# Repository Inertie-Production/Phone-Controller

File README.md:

# Phone Controller

This is a phone controller design inspired by the Nintendo 3DS. We created this controller because we wanted to make a cheap and pocketable phone controller while learning a lot of new stuff in the process! 
You can view and download the 3D model [on our Onshape][onshape].

On this github, you will find the pcb source files & gerbers, the code that
needs to be loaded on the controller and a BOM.

Once built, to use this controller, you can just clamp your phone on it, turn the power on with the switch and connect to it via bluetooth. 
Despite being very thin, this controller includes all the features of a full-size controller :
- 11 buttons with silent mechanical switches
- A D-pad
- 2 dual-axis joysticks
- 2 analog Hall effect triggers or 2 mechanical switches triggers
The 4 buttons on the back of the controller are the sticks buttons and the bumpers.

Every file of this repository and the Onshape project are licensied under the
GPL v3 license, see [`LICENSE`](./LICENSE) for details.

[onshape]: https://cad.onshape.com/documents/3e0c9ef397f91415fa372e0c/w/6f6e95703b5b2ee9676d2bfe/e/8a00a41f1ee7d469ca8e343f?renderMode=0&uiState=69529d2b1ac4d36407fdba0f

## Screenshots

## BOM

| Type | Name | Description | Qtt needed | Link |
|------|------|-------------|------------|------|
|Sticks|New 3DS XL Sticks|Nintendo new 3DS XL joysticks|2|2: https://www.alibaba.com/product-detail/Analog-Joystick-for-New-3DS-XL_1600274819879.html ; https://fr.aliexpress.com/item/1005006359586643.html + https://www.alibaba.com/product-detail/Thumb-Stick-for-3DS-3DS-XL_1601603454755.html?spm=a2700.prosearch.normal_offer.d_image.439067af8KJ20J&priceId=0518491792cb4dbdbbd4ce53df52cdd5 |
|Screws|M1.4|Nintendo 3DS joystick screws (8mm Long x 1.5mm x 2.5mm) | 4 | https://fr.aliexpress.com/item/1005002364189187.html |
| | M2|4mm countersunk screws (for closing the back panel)|9|https://fr.aliexpress.com/item/1005008709978631.html |
||M2.5|5mm round/dome screws (max head height: 1.8mm) to fix the PCB|5|https://fr.aliexpress.com/item/1005008709978631.html |
|Buttons|SS-12D00 |SS-12D00 2mm shaft slide switch (power)|1|https://fr.aliexpress.com/item/1005008489387043.html |
||Buttons|6x6x3.5mm 2 pins (silent) mouse switches (ex: HUANO Mute Button 6 × 6 × 3.5mm; Kailh Mini 6.2mm Silent Micro Switches)|11|https://fr.aliexpress.com/item/1005005681410178.html |
||SKRWADE030|SKRWADE030 tactile buttons|4|https://fr.aliexpress.com/item/4001125555481.html |
|Triggers|SS49E|SS49E Hall effect sensors|2|https://fr.aliexpress.com/item/1005006001710265.html |
||Magnets|round 5x2mm magnets|2|https://fr.aliexpress.com/item/1005010155029417.html |
||Springs|springs (15×4mm)|2|https://fr.aliexpress.com/item/1005005402501364.html |
|Electronic|603030|603030 LiPo battery (30 × 30 × 6mm)|1|https://www.alibaba.com/product-detail/Lipo-603030-3-7V-600mAh-Rechargeable_1601168807381.html ; https://fr.aliexpress.com/item/1005007958724149.html |
||Resistors|10kΩ resistor (0805)|4|https://fr.aliexpress.com/item/1005006144658512.html |
|||200 kΩ resistors (0805)|2|https://fr.aliexpress.com/item/1005008666573344.html |
||BAT54C|BAT54C diodes|8|https://fr.aliexpress.com/item/1005006228736157.html |
||Seeed studio|Seeed Studio XIAO ESP32-S3 Plus and an antenna|1|https://www.seeedstudio.com/Seeed-Studio-XIAO-ESP32S3-Plus-p-6361.html ; https://fr.aliexpress.com/item/1005008329745247.html |
||100 nF 0805|100 nF capacitor (0805)|1|https://fr.aliexpress.com/item/1005006142309480.html
||PCB|The PCB|1|https://cart.jlcpcb.com/fr/quote?stencilLayer=2&stencilWidth=100&stencilLength=100&stencilCounts=5&plateType=1&spm=Jlcpcb.Homepage.1010 |
|Plastic|3D printer filament|in grams, full estimation to check|300|

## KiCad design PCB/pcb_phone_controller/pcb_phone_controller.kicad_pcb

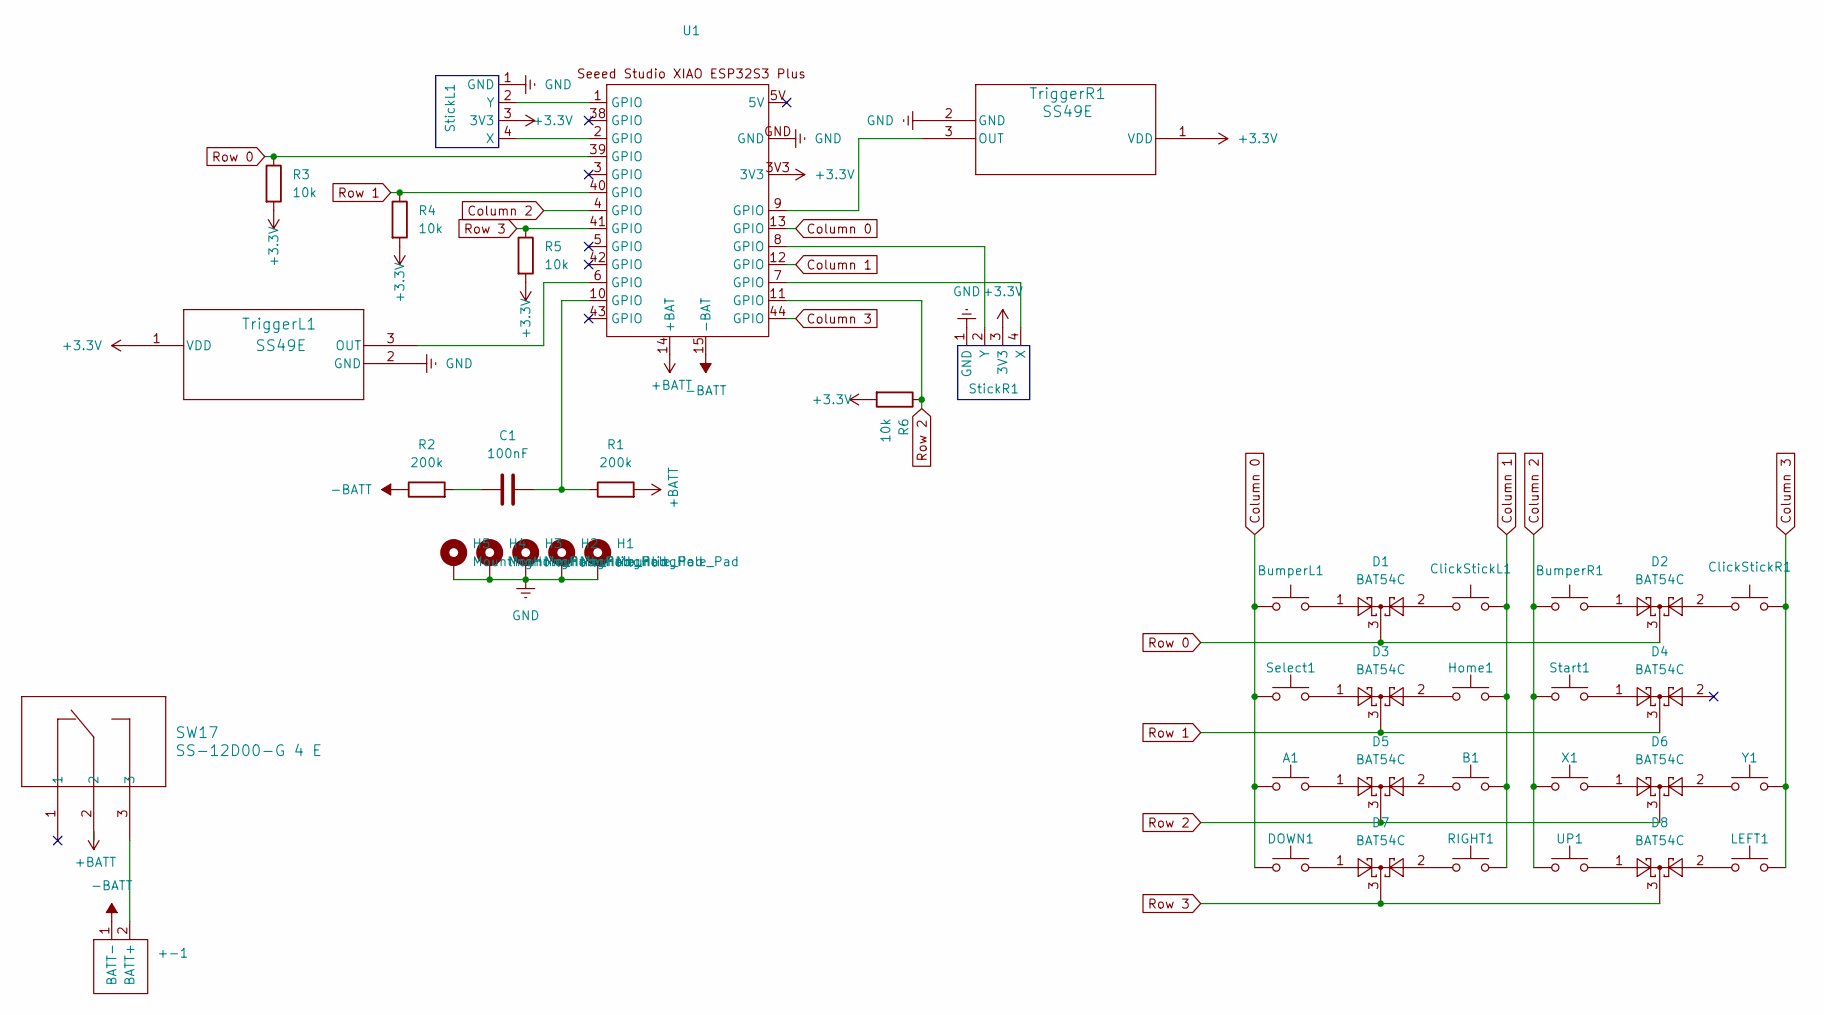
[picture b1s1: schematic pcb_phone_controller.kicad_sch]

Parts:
+-1: Battery_connection
A1: KAILH-MINI-SILENT-SWITCH
B1: KAILH-MINI-SILENT-SWITCH
BumperL1: Thin membrane button; SKRWADE030
BumperR1: Thin membrane button; SKRWADE030
C1: 100nF; C_0805_2012Metric_Pad1.18x1.45mm_HandSolder
ClickStickL1: Thin membrane button; SKRWADE030
ClickStickR1: Thin membrane button; SKRWADE030
D1, D2, D3, D4, D5, D6, D7, D8: BAT54C; SOT-23
DOWN1: KAILH-MINI-SILENT-SWITCH
H1, H2, H3, H4, H5: MountingHole_Pad; MountingHole_2.7mm_M2.5_ISO14580_Pad
Home1: KAILH-MINI-SILENT-SWITCH
LEFT1: KAILH-MINI-SILENT-SWITCH
R1, R2: 200k; R_0805_2012Metric_Pad1.20x1.40mm_HandSolder
R3, R4, R5, R6: 10k; R_0805_2012Metric_Pad1.20x1.40mm_HandSolder
RIGHT1: KAILH-MINI-SILENT-SWITCH
SW17: SS-12D00-G 4 E; 1P2T_SS-12D00_CNK
Select1: KAILH-MINI-SILENT-SWITCH
Start1: KAILH-MINI-SILENT-SWITCH
StickL1: PinHeader_1x04_P2.54mm_Vertical
StickR1: PinHeader_1x04_P2.54mm_Vertical
TriggerL1: SS49E; ss49e
TriggerR1: SS49E; ss49e
U1: Seeed Studio XIAO ESP32S3 Plus
UP1: KAILH-MINI-SILENT-SWITCH
X1: KAILH-MINI-SILENT-SWITCH
Y1: KAILH-MINI-SILENT-SWITCH

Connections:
+3.3V: R3.2, R4.2, R5.2, R6.2, StickL1.3 (3V3), StickR1.3 (3V3), TriggerL1.1 (VDD), TriggerR1.1 (VDD), U1.3V3
+BATT: R1.2, SW17.2, U1.14 (+BAT)
-BATT: +-1.1 (BATT-), R2.1, U1.15 (-BAT)
Column 0: A1.1, BumperL1.1, DOWN1.1, Select1.1, U1.13 (GPIO)
Column 1: B1.2, ClickStickL1.2, Home1.2, RIGHT1.2, U1.12 (GPIO)
Column 2: BumperR1.1, Start1.1, U1.4 (GPIO), UP1.1, X1.1
Column 3: ClickStickR1.2, LEFT1.2, U1.44 (GPIO), Y1.2
GND: H1.1, H2.1, H3.1, H4.1, H5.1, StickL1.1 (GND), StickR1.1 (GND), TriggerL1.2 (GND), TriggerR1.2 (GND), U1.GND
unnamed: +-1.2 (BATT+), SW17.3
unnamed: A1.2, D5.1
unnamed: B1.1, D5.2
unnamed: BumperL1.2, D1.1
unnamed: BumperR1.2, D2.1
unnamed: C1.1, R1.1, U1.10 (GPIO)
unnamed: C1.2, R2.2
unnamed: ClickStickL1.1, D1.2
unnamed: ClickStickR1.1, D2.2
unnamed: D3.1, Select1.2
unnamed: D3.2, Home1.1
unnamed: D4.1, Start1.2
unnamed: D6.1, X1.2
unnamed: D6.2, Y1.1
unnamed: D7.1, DOWN1.2
unnamed: D7.2, RIGHT1.1
unnamed: D8.1, UP1.2
unnamed: D8.2, LEFT1.1
unnamed: StickL1.4 (X), U1.2 (GPIO)
unnamed: StickL1.2 (Y), U1.1 (GPIO)
unnamed: StickR1.4 (X), U1.7 (GPIO)
unnamed: StickR1.2 (Y), U1.8 (GPIO)
unnamed: TriggerL1.3 (OUT), U1.6 (GPIO)
unnamed: TriggerR1.3 (OUT), U1.9 (GPIO)
Row 0: D1.3, D2.3, R3.1, U1.39 (GPIO)
Row 1: D3.3, D4.3, R4.1, U1.40 (GPIO)
Row 2: D5.3, D6.3, R6.1, U1.11 (GPIO)
Row 3: D7.3, D8.3, R5.1, U1.41 (GPIO)

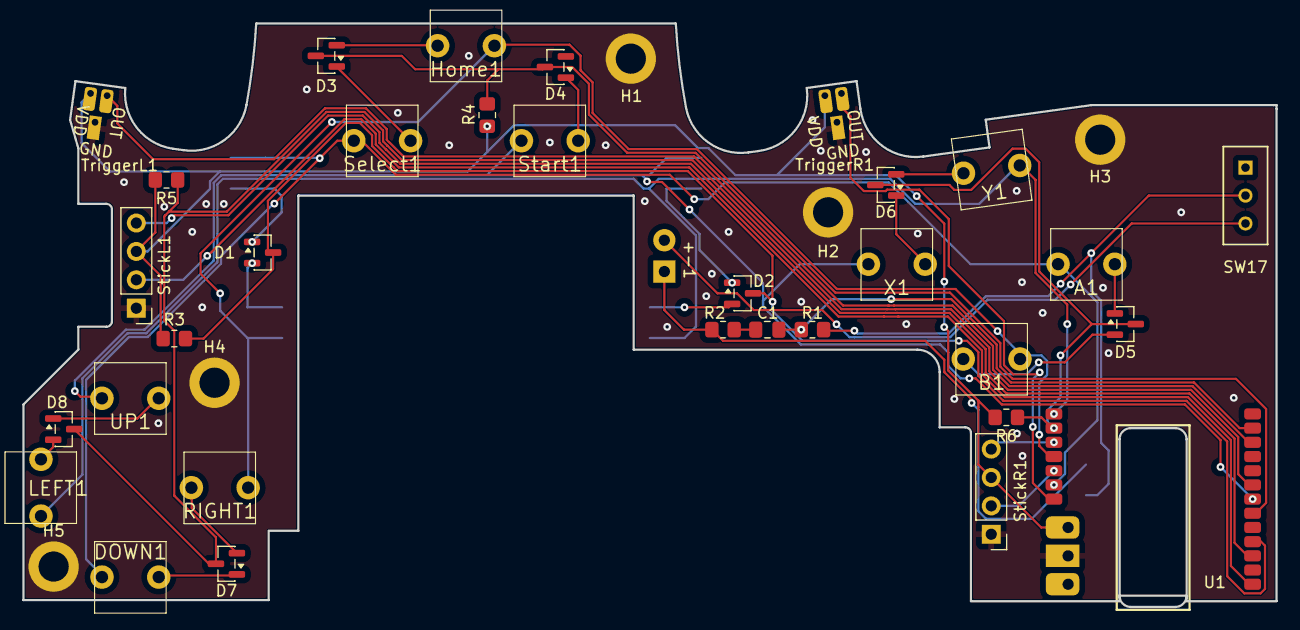
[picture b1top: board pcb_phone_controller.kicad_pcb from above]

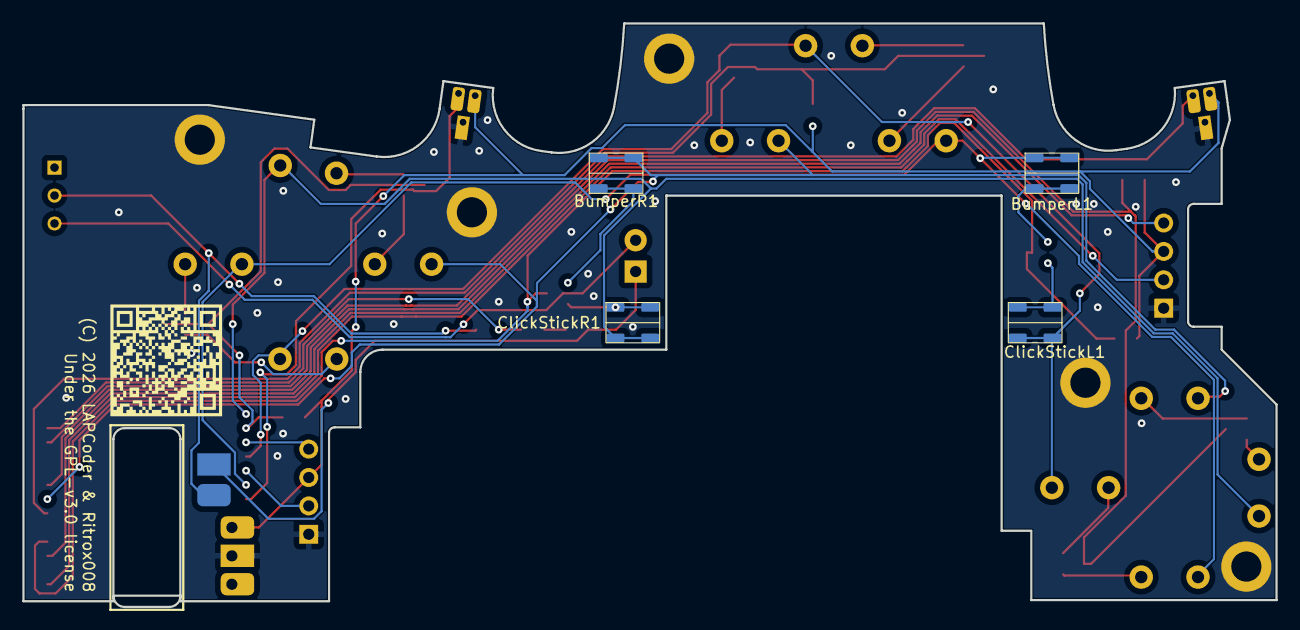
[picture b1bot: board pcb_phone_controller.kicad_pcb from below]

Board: 2 copper layers, 112.1 x 52.2 mm, 42 parts (4 on the bottom side), 36 nets.

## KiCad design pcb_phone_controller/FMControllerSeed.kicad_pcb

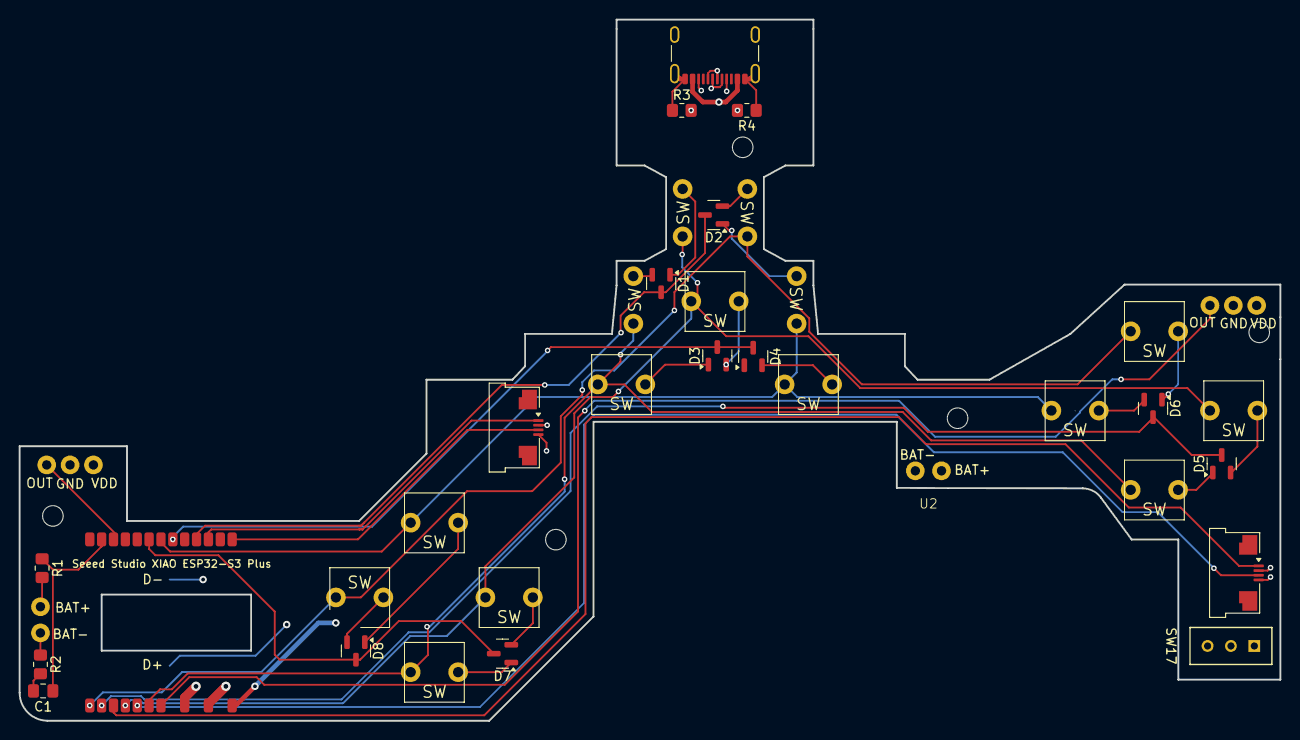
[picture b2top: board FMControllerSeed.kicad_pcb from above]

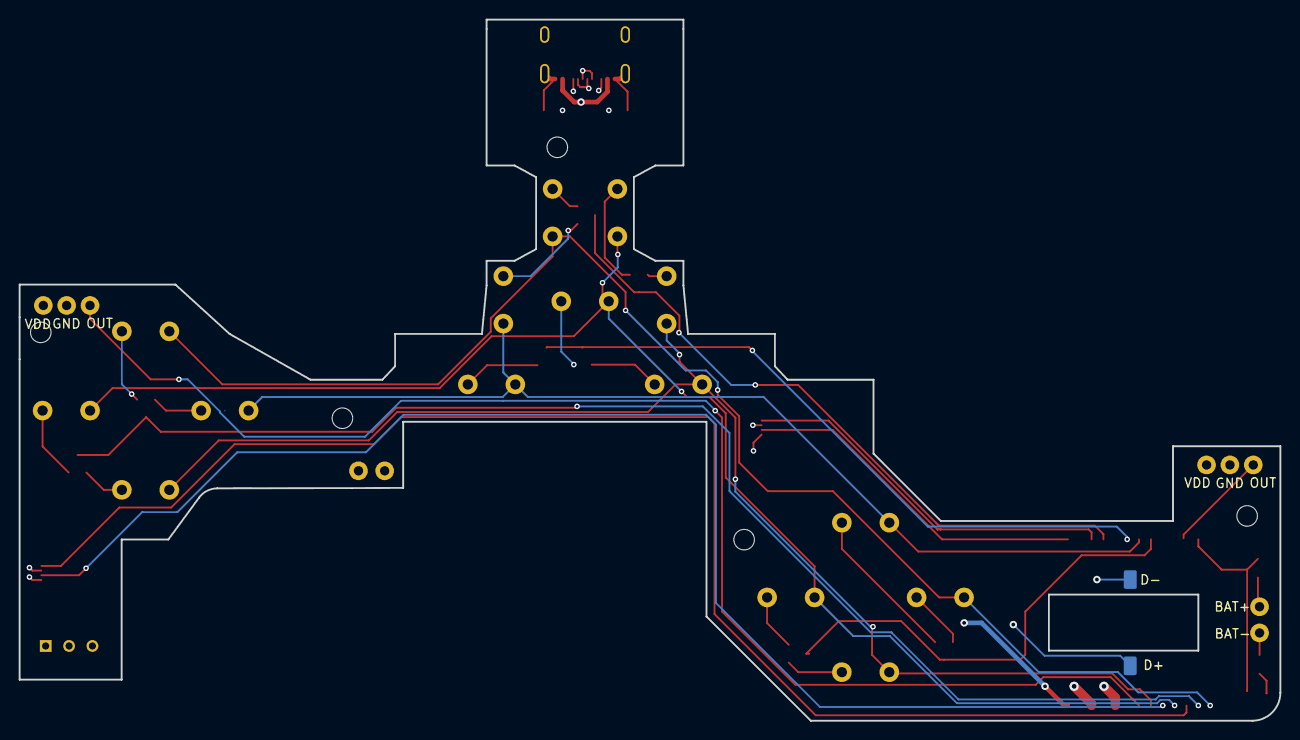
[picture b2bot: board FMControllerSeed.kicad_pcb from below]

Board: 4 copper layers, 135.0 x 75.0 mm, 39 parts (4 on the bottom side), 41 nets.

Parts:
A1: KAILH-MINI-SILENT-SWITCH
B1: KAILH-MINI-SILENT-SWITCH
BumperL1: KAILH-MINI-SILENT-SWITCH
BumperR1: KAILH-MINI-SILENT-SWITCH
C1: 100nF; C_0805_2012Metric_Pad1.18x1.45mm_HandSolder
D1, D2, D3, D4, D5, D6, D7, D8: BAT54C; SOT-23
DOWN1: KAILH-MINI-SILENT-SWITCH
Home1: KAILH-MINI-SILENT-SWITCH
J1: USB_C_Receptacle_USB2.0_16P; USB_C_Receptacle_GCT_USB4105-xx-A_16P_TopMnt_Horizontal
J2, J2#2: USB_C_Connection
LEFT1: KAILH-MINI-SILENT-SWITCH
R1, R2: 100k; R_0805_2012Metric_Pad1.20x1.40mm_HandSolder
R3, R4: 5KΩ; R_0805_2012Metric_Pad1.20x1.40mm_HandSolder
RIGHT1: KAILH-MINI-SILENT-SWITCH
SW17: SS-12D00-G 4 E; 1P2T_SS-12D00_CNK
Select1: KAILH-MINI-SILENT-SWITCH
Start1: KAILH-MINI-SILENT-SWITCH
StickL1: Amphenol_F32Q-1A7x1-11004_1x04-1MP_P0.5mm_Horizontal
StickL2: KAILH-MINI-SILENT-SWITCH
StickR1: Amphenol_F32Q-1A7x1-11004_1x04-1MP_P0.5mm_Horizontal
StickR2: KAILH-MINI-SILENT-SWITCH
TriggerL1: SS49E; SEN3_SS49E_HNW
TriggerR1: SS49E; SEN3_SS49E_HNW
U1: Seeed Studio XIAO ESP32S3 Plus
U2, U3: Battery_connection
UP1: KAILH-MINI-SILENT-SWITCH
X1: KAILH-MINI-SILENT-SWITCH
Y1: KAILH-MINI-SILENT-SWITCH

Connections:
+3.3V: StickL1.2 (GND), StickR1.2 (GND), TriggerL1.1 (VDD), TriggerR1.1 (VDD), U1.3V3
+BAT: R1.2, SW17.2, U3.2 (BAT+)
-BATT: R2.1, U2.1 (BAT-), U3.1 (BAT-)
Column 0: A1.1, BumperL1.1, DOWN1.1, Select1.1, U1.13 (GPIO)
Column 1: B1.1, Home1.1, RIGHT1.1, StickL2.1, U1.12 (GPIO)
Column 2: BumperR1.1, Start1.1, U1.4 (GPIO), UP1.1, X1.1
Column 3: LEFT1.1, StickR2.1, U1.44 (GPIO), Y1.1
D+: J1.A6 (D+), J1.B6 (D+), J2.B5
D-: J1.A7 (D-), J1.B7 (D-), J2#2.B5 (CC2)
GND: J1.A1 (GND), J1.A12 (GND), J1.B1 (GND), J1.B12 (GND), J1.S1 (SHIELD), R3.1, R4.1, StickL1.4 (3V3), StickR1.4 (3V3), TriggerL1.2 (GND), TriggerR1.2 (GND), U1.GND
unnamed: A1.2, D5.1
unnamed: B1.2, D5.2
unnamed: BumperL1.2, D1.2
unnamed: BumperR1.2, D2.1
unnamed: C1.1, R1.1, U1.10 (GPIO)
unnamed: C1.2, R2.2
unnamed: D1.1, StickL2.2
unnamed: D2.2, StickR2.2
unnamed: D3.1, Select1.2
unnamed: D3.2, Home1.2
unnamed: D4.2, Start1.2
unnamed: D6.1, Y1.2
unnamed: D6.2, X1.2
unnamed: D7.1, DOWN1.2
unnamed: D7.2, RIGHT1.2
unnamed: D8.1, UP1.2
unnamed: D8.2, LEFT1.2
unnamed: J1.A5 (CC1), R4.2
unnamed: J1.B5 (CC2), R3.2
unnamed: StickL1.1 (X), U1.2 (GPIO)
unnamed: StickL1.3 (Y), U1.1 (GPIO)
unnamed: StickR1.1 (X), U1.7 (GPIO)
unnamed: StickR1.3 (Y), U1.8 (GPIO)
unnamed: TriggerL1.3 (OUT), U1.6 (GPIO)
unnamed: TriggerR1.3 (OUT), U1.9 (GPIO)
unnamed: SW17.3, U2.2 (BAT+)
Row 0: D1.3, D2.3, U1.39 (GPIO)
Row 1: D3.3, D4.3, U1.40 (GPIO)
Row 2: D5.3, D6.3, U1.11 (GPIO)
Row 3: D7.3, D8.3, U1.41 (GPIO)
VBUS: J1.A4 (VBUS), J1.A9 (VBUS), J1.B4 (VBUS), J1.B9 (VBUS), U1.5V

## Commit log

2025-12-23 Add unreviewed untested code
2025-12-25 Add library
    ESP32-BLE-Gamepad 7.3
2025-12-27 Add the PCB
2025-12-28 PCB cleanup (libs and traces)
2025-12-29 PCB shape and reroute to make space for sticks
2025-12-29 PCB shape refinement
2025-12-29 Enhance README with design inspiration and model link
    Added a detailed description and a link to the 3D model.
2025-12-29 Revise BOM with updated components and specifications
    Updated the BOM to reflect changes in joystick types, added components including magnets and springs, and revised screw specifications.
2025-12-29 Revise README for Phone Controller details
    Updated the title and added information about PCB source files and code.
2025-12-29 folder name
2025-12-29 Update 3D model link format in README
2026-01-02 Various fixes Add license on PCB Fix the hole Fix DRC Fix code tree Put back the drc-passed hall effect pads Beautify the BOM Add folders
2026-01-02 Add a gitignore and enhance the readme
2026-01-02 Fix typo in license name from 'GLP' to 'GPL'
2026-01-02 Update .gitignore and the Gerber files
2026-01-02 Add pads to connect the battery to the µcontroller + add assembly guide
2026-01-03 Add a 3D model for the TTP223
2026-01-03 Quickfix: replace the labels on the PCB
2026-01-05 Change capacitives buttons to digitals ones and add real pullup
2026-01-05 Add a 3D model for the back buttons
2026-01-06 Update the BOM to match the newest requirements
2026-01-06 Prepare the Blender by adding LFS
2026-01-06 Add the Blender
2026-01-06 Im a bit stupid
2026-01-06 Add the lfs textures (i hope)
2026-01-06 Small fixes. The code is still not tested, hardware "supply" "issue" It means we don't have the seeed studio right now.
2026-01-11 Upddate the blender
2026-01-11 Fix to avoid storing txt in lfs
2026-01-11 Readd the INFO file
2026-01-11 Fix .gitattributes
2026-01-11 Update the BOM to a nice and clean spreadsheet
2026-01-11 Add the PCB in the BOM and make the PCB smaller
2026-01-14 Update a bit the BOM and the gitignore
2026-01-16 Reroute the PCB to move the buttons
2026-01-18 Modify a bit the PCB
2026-03-30 Add images to README for project visualization
2026-03-30 Update README with BOM and button layout details
    Added a BOM to the README and clarified the button layout description.
2026-03-30 Fix duplicate image tag in README
    Removed duplicate image tag for the front-closed view and adjusted the formatting.
2026-03-30 Fix image tag in README.md
2026-03-30 Enhance README with detailed controller features
    Expanded description of controller features and clarified button functionality.
2026-03-30 Enhance README with project details and usage info
    Expanded the project description and added usage instructions.
2026-03-30 Add BOM in readme
2026-03-31 step for 3d printed parts

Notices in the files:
PCB/pcb_phone_controller/pcb_phone_controller.kicad_pcb:
(C) 2026 LAPCoder & Ritrox008
Under the GPL-v3.0 license
